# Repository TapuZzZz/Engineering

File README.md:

# ═══════════════════════════════════════════════════════════════════════════════
#                         🔧 ALGORITHM ENGINEERING GUIDE 🔧
# ═══════════════════════════════════════════════════════════════════════════════

> *A comprehensive reference for data structures, algorithms, and graph theory implementations*

---

## 📚 Data Structures

### Stack (LIFO - Last In, First Out)
```
    Push: 3      ┌─────┐
    Push: 2  →   │  3  │
    Push: 1      │  2  │
    Pop: 1       │  1  │
                 └─────┘
```
**Use Cases:** Function call stack, undo/redo, parentheses matching, DFS

---

### Queue (FIFO - First In, First Out)
```
    Enqueue: A   A → B → C → NULL
    Enqueue: B   
    Enqueue: C   (Head)
    Dequeue: A
```
**Use Cases:** BFS, task scheduling, printer queue, message handling

---

### Linked Lists
```
Linear Linked List (LLL)
    ┌─────┬───┐  ┌─────┬───┐  ┌─────┬───┐
    │ 1   │ •─┼─→│ 2   │ •─┼─→│ 3   │ ∅ │
    └─────┴───┘  └─────┴───┘  └─────┴───┘

Circular Linked List (CLLL)
    ┌─────┬───┐  ┌─────┬───┐  ┌─────┬───┐
    │ 1   │ •─┼─→│ 2   │ •─┼─→│ 3   │ •─┐
    └─────┴───┘  └─────┴───┘  └─────┴───┘
         ↑────────────────────────────────┘

Doubly Linked List (DLLL)
    ┌─────┬───┬───┐  ┌─────┬───┬───┐  ┌─────┬───┬───┐
    │ 1   │ ∅ │ •─┼─→│ 2   │ •─┼─→│ 3   │ •─┼─→│ ∅ │
    │     │ ←─┼─│   │     │ ←─┼─│   │     │ ←─┼─│
    └─────┴───┴───┘  └─────┴───┴───┘  └─────┴───┴───┘
```

---

### Trees

#### Binary Tree
```
           ┌─────┐
           │  1  │
         ┌─┴──┬──┴─┐
        ┌─┴─┐┌─┴─┐ │
        │ 2 ││3  │ │
       ┌┴─┐ ││    │ │
       │4 │ ││    │ │
       └──┘ └┘    └─┘
```
**Time Complexity:** O(log n) average, O(n) worst case

#### AVL Tree (Self-Balancing)
```
        ┌────┴────┐
        │    20   │ ↔ Height: 2
      ┌─┴─┐   ┌───┴─┐
      │10 │   │ 30  │ ↔ Height: 1
     ┌┴─┐ │    │  └──┴──┐
     │5 │ │   │15│    40│
```
**Time Complexity:** O(log n) guaranteed

#### K-ary Tree
```
         ┌──────┴──────┐
         │      1      │ K=3 (ternary)
    ┌────┼────┬──────┐
    │    │    │      │
   ┌2┐  ┌3┐  ┌4┐    ┌5┐
```

#### Heap (Binary Heap)
```
Min Heap              Max Heap
      1                    100
    ┌─┴─┐              ┌──┴──┐
    2   3              80    70
   ┌┴┐ ┌┴┐            ┌┴┐  ┌─┴┐
   4 5 6 7           50 40 30 20

Array: [1,2,3,4,5,6,7]    [100,80,70,50,40,30,20]
```
**Use Cases:** Priority queues, heapsort

---

## 🔄 Graph Theory

### Graph Representations
```
Adjacency Matrix          Adjacency List
  0 1 2 3                 0: [1, 2]
0[0 1 1 0]                1: [0, 3]
1[1 0 1 1]                2: [0, 3]
2[1 1 0 1]                3: [1, 2]
3[0 1 1 0]
```

### Graph Traversal

#### Breadth-First Search (BFS)
```
Start: 0
Level 0:  [0]
Level 1:  [1, 2]
Level 2:  [3, 4, 5]
Level 3:  [6, 7, 8]

Use: Shortest path, level order, connected components
```

#### Depth-First Search (DFS)
```
Start: 0
Path 1: 0 → 1 → 3 → (backtrack)
Path 2: 0 → 2 → 4 → 5 → (backtrack)

Use: Topological sort, cycle detection, connected components
```

### Shortest Path Algorithms

#### Dijkstra's Algorithm
```
Finds shortest path from source to all vertices
Time: O((V + E) log V)
Constraints: Non-negative weights only

     2      3
  A ──→ B ──→ C
  │           ↑
  │─────5─────│
```

#### Bellman-Ford Algorithm
```
Finds shortest path, handles negative weights
Time: O(V × E)
Use: Graphs with negative edge weights

     2      3
  A ──→ B ──→ C
  │          ↑
  │────-1────│
```

#### Floyd-Warshall Algorithm
```
All pairs shortest paths
Time: O(V³)
Space: O(V²)

Creates distance matrix for all vertex pairs
```

### Minimum Spanning Tree

#### Kruskal's Algorithm
```
1. Sort edges by weight
2. Add edge if no cycle formed
3. Continue until all vertices connected

Time: O(E log E)
```

#### Prim's Algorithm
```
1. Start from vertex
2. Add minimum weight edge connecting tree to new vertex
3. Repeat until all vertices in tree

Time: O(V²) or O(E log V)
```

### Topological Sort (DAG)
```
Prerequisites: 0 → 1 → 3
              0 → 2 → 3

Order: 0, 1/2, 2/1, 3

Use: Task scheduling, build systems, course prerequisites
```

---

## 📊 Sorting Algorithms

### Comparison-Based Sorts

| Algorithm | Best | Average | Worst | Space | Stable |
|-----------|------|---------|-------|-------|--------|
| **Bubble Sort** | O(n) | O(n²) | O(n²) | O(1) | ✓ |
| **Selection Sort** | O(n²) | O(n²) | O(n²) | O(1) | ✗ |
| **Insertion Sort** | O(n) | O(n²) | O(n²) | O(1) | ✓ |
| **Shell Sort** | O(n) | O(n log² n) | O(n²) | O(1) | ✗ |
| **Merge Sort** | O(n log n) | O(n log n) | O(n log n) | O(n) | ✓ |
| **Quick Sort** | O(n log n) | O(n log n) | O(n²) | O(log n) | ✗ |
| **Heap Sort** | O(n log n) | O(n log n) | O(n log n) | O(1) | ✗ |

### Non-Comparison Sorts

| Algorithm | Time | Space | Conditions |
|-----------|------|-------|-----------|
| **Counting Sort** | O(n + k) | O(k) | Non-negative integers |
| **Bucket Sort** | O(n + k) avg | O(n + k) | Uniformly distributed |
| **Radix Sort** | O(d × n) | O(n + k) | Fixed number of digits |

### Visualization Example: Merge Sort
```
[38, 27, 43, 3, 9, 82, 10]
        ↓ Divide
[38,27] [43,3] [9,82] [10]
        ↓ Merge
[27,38] [3,43] [9,82] [10]
        ↓ Merge Again
    [3,27,38,43]  [9,10,82]
        ↓ Final Merge
  [3,9,10,27,38,43,82]
```

---

## 🔍 Search Algorithms

### Binary Search
```
Sorted Array: [1, 3, 5, 7, 9, 11, 13, 15]
Search for 7:

  L: 0         M: 3         R: 7
  [1, 3, 5, 7, 9, 11, 13, 15]
           ↑
        Found!

Time Complexity: O(log n)
Space Complexity: O(1) or O(log n) recursive
```

---

## 📈 Complexity Analysis

### Big O Notation Hierarchy
```
O(1) ──────────────── Constant
      ↓
O(log n) ───────────── Logarithmic
      ↓
O(n) ───────────────── Linear
      ↓
O(n log n) ─────────── Linearithmic
      ↓
O(n²) ───────────────── Quadratic
      ↓
O(n³) ───────────────── Cubic
      ↓
O(2ⁿ) ───────────────── Exponential
      ↓
O(n!) ──────────────── Factorial
```

### Graph Complexity

| Operation | Adjacency Matrix | Adjacency List |
|-----------|-----------------|----------------|
| Add Edge | O(1) | O(1) |
| Remove Edge | O(1) | O(V) |
| Add Vertex | O(V²) | O(1) |
| Check Edge | O(1) | O(V) |
| Space | O(V²) | O(V + E) |

---

## 💡 Quick Reference

### When to Use Each Structure

```
🔹 Stack → Recursion, undo/redo, parsing
🔹 Queue → BFS, task scheduling
🔹 Linked List → Insertion/deletion heavy workloads
🔹 Tree → Hierarchical data, searching
🔹 Heap → Priority queue, k-th largest/smallest
🔹 Hash Table → Fast lookup, mapping
🔹 Graph → Networks, recommendations, shortest paths
```

### Algorithm Selection Guide

| Problem | Choose | Why |
|---------|--------|-----|
| **Shortest Path** | Dijkstra | Non-negative weights |
| **Shortest Path (negative)** | Bellman-Ford | Handles negatives |
| **All Pairs Shortest** | Floyd-Warshall | Complete info needed |
| **Minimum Span Tree** | Kruskal | Edge-based approach |
| **Task Order** | Topological Sort | DAG processing |
| **Quick Sorting** | Quick Sort | Average O(n log n) |
| **Stable Sort** | Merge Sort | Preserve order |
| **Small Arrays** | Insertion Sort | Low overhead |
| **Search Sorted** | Binary Search | O(log n) lookup |

---

## ✨ Key Takeaways

1. **Choose your tools wisely** - The right data structure determines efficiency
2. **Know your complexity** - Understand best/average/worst cases
3. **Trade-offs matter** - Time vs space, implementation vs performance
4. **Test edge cases** - Empty inputs, single elements, duplicates
5. **Profile first** - Optimize bottlenecks, not everything
6. **Document well** - Future you (and others) will thank you

---

```
╔═══════════════════════════════════════════════════════════════════════════════╗
║                     Happy Coding! 🚀 Build Beautiful Code                     ║
╚═══════════════════════════════════════════════════════════════════════════════╝
```

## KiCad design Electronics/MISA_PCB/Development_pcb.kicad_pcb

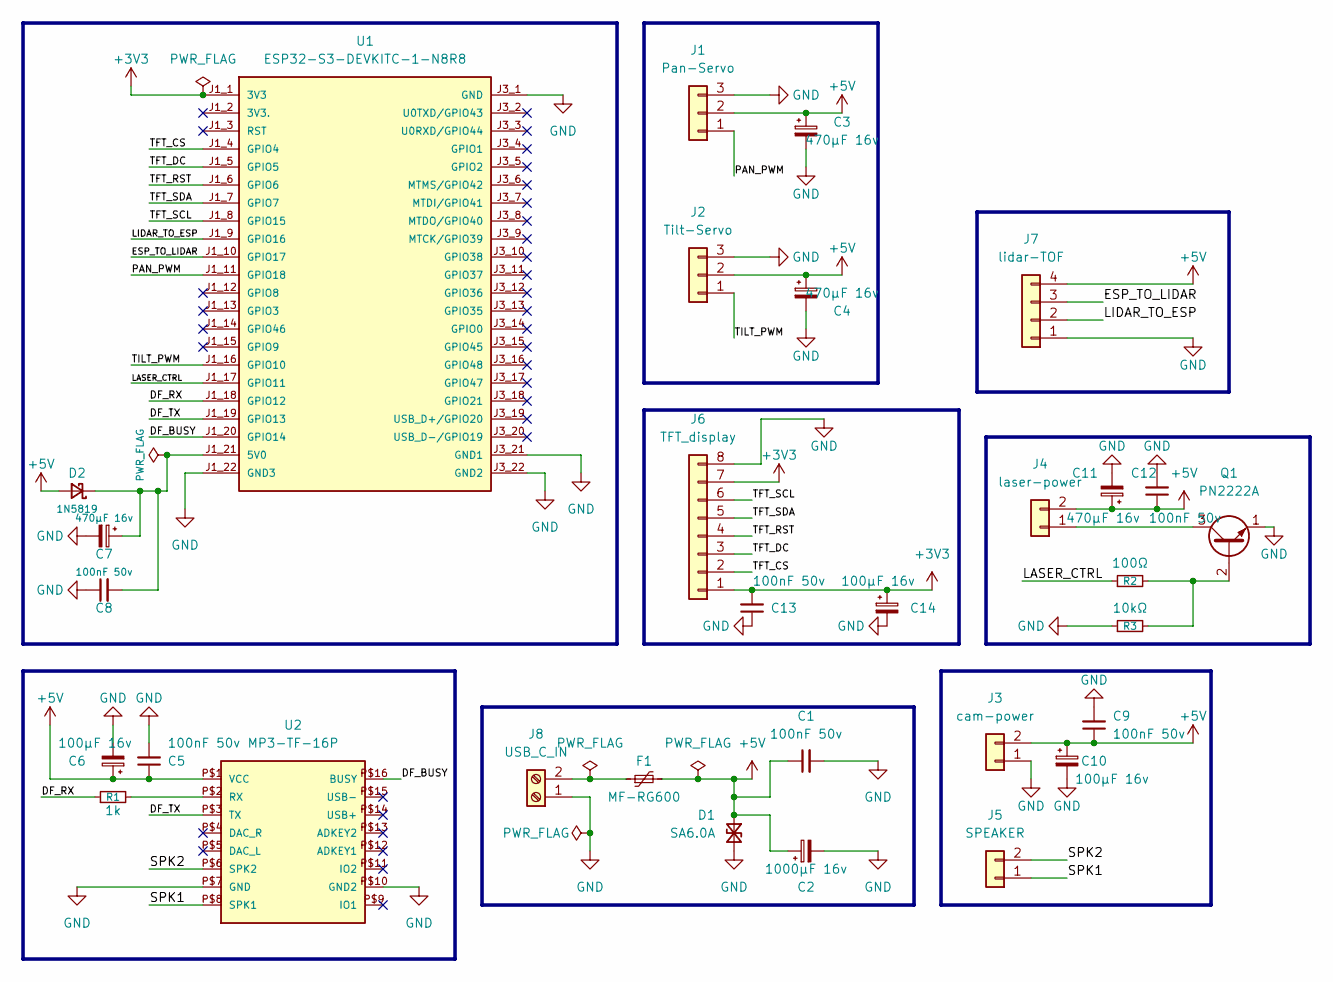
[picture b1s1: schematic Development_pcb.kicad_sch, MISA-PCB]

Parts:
C1, C5, C8, C9, C12, C13: 100nF 50v; C_Disc_D5.0mm_W2.5mm_P2.50mm
C2: 1000µF 16v; CP_Radial_D12.5mm_P5.00mm
C3, C4, C7, C11: 470µF 16v; CP_Radial_D8.0mm_P3.50mm
C6, C10: 100µF 16v; CP_Radial_D6.3mm_P2.50mm
C14: 100µF 16v; CP_Radial_D5.0mm_P2.50mm
D1: SA6.0A; D_DO-15_P10.16mm_Horizontal
D2: 1N5819; D_DO-41_SOD81_P10.16mm_Horizontal
F1: MF-RG600; Fuse_Bourns_MF-RG600
J1: Pan-Servo; JST_XH_B3B-XH-A_1x03_P2.50mm_Vertical
J2: Tilt-Servo; JST_XH_B3B-XH-A_1x03_P2.50mm_Vertical
J3: cam-power; JST_XH_B2B-XH-A_1x02_P2.50mm_Vertical
J4: laser-power; JST_XH_B2B-XH-A_1x02_P2.50mm_Vertical
J5: SPEAKER; JST_XH_B2B-XH-A_1x02_P2.50mm_Vertical
J6: TFT_display; JST_XH_B8B-XH-A_1x08_P2.50mm_Vertical
J7: lidar-TOF; JST_XH_B4B-XH-A_1x04_P2.50mm_Vertical
J8: USB_C_IN; TerminalBlock_Xinya_XY308-2.54-2P_1x02_P2.54mm_Horizontal
Q1: PN2222A; TO-92_Inline
R1: 1k; R_Axial_DIN0207_L6.3mm_D2.5mm_P10.16mm_Horizontal
R2: 100Ω; R_Axial_DIN0207_L6.3mm_D2.5mm_P2.54mm_Vertical
R3: 10kΩ; R_Axial_DIN0207_L6.3mm_D2.5mm_P2.54mm_Vertical
U1: ESP32-S3-DEVKITC-1-N8R8; ESP32-S3-DevKitC-1_Socket
U2: MP3-TF-16P

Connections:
+3V3: C13.2, C14.1, J6.1, J6.7, U1.J1_1 (3V3)
+5V: C1.1, C2.1, C3.1, C4.1, C5.1, C6.1, C9.1, C10.1, C11.1, C12.1, D1.1 (A1), D2.2 (A), F1.2, J1.2, J2.2, J3.2, J4.2, J7.4, U2.P$1 (VCC)
/DF_BUSY: U1.J1_20 (GPIO14), U2.P$16 (BUSY)
/DF_RX: R1.1, U1.J1_18 (GPIO12)
/DF_TX: U1.J1_19 (GPIO13), U2.P$3 (TX)
/ESP_TO_LIDAR: J7.3, U1.J1_10 (GPIO17)
/LASER_CTRL: R2.1, U1.J1_17 (GPIO11)
/LIDAR_TO_ESP: J7.2, U1.J1_9 (GPIO16)
/PAN_PWM: J1.1, U1.J1_11 (GPIO18)
/SPK1: J5.1, U2.P$8 (SPK1)
/SPK2: J5.2, U2.P$6 (SPK2)
/TFT_CS: J6.2, U1.J1_4 (GPIO4)
/TFT_DC: J6.3, U1.J1_5 (GPIO5)
/TFT_RST: J6.4, U1.J1_6 (GPIO6)
/TFT_SCL: J6.6, U1.J1_8 (GPIO15)
/TFT_SDA: J6.5, U1.J1_7 (GPIO7)
/TILT_PWM: J2.1, U1.J1_16 (GPIO10)
GND: C1.2, C2.2, C3.2, C4.2, C5.2, C6.2, C7.2, C8.1, C9.2, C10.2, C11.2, C12.2, C13.1, C14.2, D1.2 (A2), J1.3, J2.3, J3.1, J6.8, J7.1, J8.1, Q1.1 (E), R3.1, U1.J1_22 (GND3), U1.J3_1 (GND), U1.J3_21 (GND1), U1.J3_22 (GND2), U2.P$7 (GND), U2.P$10 (GND2)
unnamed: C7.1, C8.2, D2.1 (K), U1.J1_21 (5V0)
unnamed: J4.1, Q1.3 (C)
unnamed: F1.1, J8.2
unnamed: Q1.2 (B), R2.2, R3.2
unnamed: R1.2, U2.P$2 (RX)

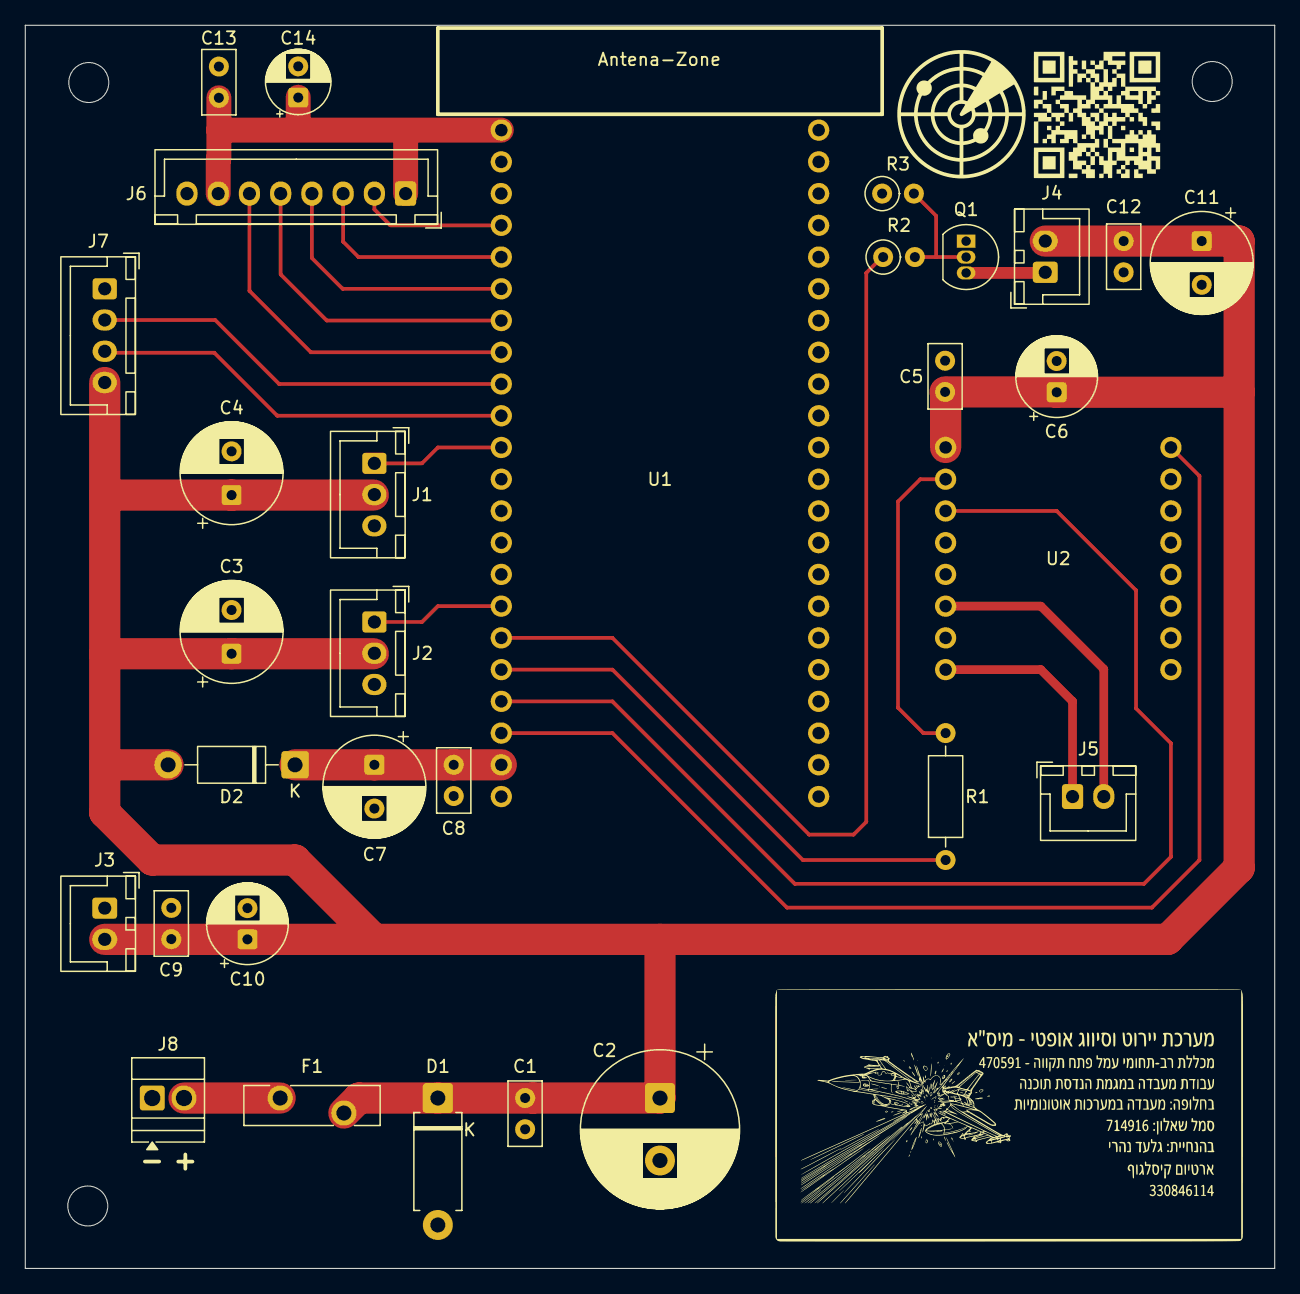
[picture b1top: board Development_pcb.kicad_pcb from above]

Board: 2 copper layers, 100.0 x 99.5 mm, 31 parts (0 on the bottom side), 23 nets.

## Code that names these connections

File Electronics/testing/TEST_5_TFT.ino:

// =================================================================
//  TEST 5 - TFT SCREEN (ST7735) ONLY
//
//  WIRING: CS = GPIO11, RST = GPIO12, DC = GPIO9, MOSI = GPIO10, SCK = GPIO15
// =================================================================

#include <SPI.h>
#include <Adafruit_GFX.h>
#include <Adafruit_ST7735.h>

#define TFT_CS   11
#define TFT_RST  12
#define TFT_DC   9
#define TFT_MOSI 10
#define TFT_SCK  15

class TftWithOffset : public Adafruit_ST7735 {
public:
  TftWithOffset(SPIClass* spiBus, int8_t csPin, int8_t dcPin, int8_t rstPin)
    : Adafruit_ST7735(spiBus, csPin, dcPin, rstPin) {}

  using Adafruit_ST7735::setColRowStart;
};

TftWithOffset tft = TftWithOffset(&SPI, TFT_CS, TFT_DC, TFT_RST);

const int8_t TFT_COL_OFFSET = 2;
const int8_t TFT_ROW_OFFSET = 1;

void setup() {
  Serial.begin(115200);
  delay(1000);

  Serial.println("=== TEST 5: TFT SCREEN ONLY ===");
  Serial.println("CS=11 RST=12 DC=9 MOSI=10 SCK=15");
  Serial.println("");

  pinMode(TFT_RST, OUTPUT);
  digitalWrite(TFT_RST, HIGH);
  delay(100);
  digitalWrite(TFT_RST, LOW);
  delay(100);
  digitalWrite(TFT_RST, HIGH);
  delay(100);

  SPI.begin(TFT_SCK, -1, TFT_MOSI, TFT_CS);
  SPI.setFrequency(1000000);

  tft.initR(INITR_BLACKTAB);
  tft.setRotation(1);
  tft.setColRowStart(TFT_COL_OFFSET, TFT_ROW_OFFSET);

  Serial.println("Screen initialized. Running color fill test...");

  tft.fillScreen(ST7735_RED);
  Serial.println("RED - check full panel is red, no dead areas.");
  delay(1000);

  tft.fillScreen(ST7735_GREEN);
  Serial.println("GREEN");
  delay(1000);

  tft.fillScreen(ST7735_BLUE);
  Serial.println("BLUE");
  delay(1000);

  tft.fillScreen(ST7735_WHITE);
  Serial.println("WHITE - look closely for any noisy/misaligned edge.");
  delay(1000);

  tft.fillScreen(ST7735_BLACK);

  tft.drawRect(0, 0, tft.width(), tft.height(), ST7735_YELLOW);

  tft.setTextColor(ST7735_WHITE);
  tft.setTextSize(1);
  tft.setCursor(10, 10);
  tft.print("TFT TEST OK");
  tft.setCursor(10, 25);
  tft.print("Border should be flush");
  tft.setCursor(10, 40);
  tft.print("on all 4 edges.");

  Serial.println("Border + text drawn. Check border alignment on all edges.");
  Serial.println("");
  Serial.println("=== TEST COMPLETE ===");
}

void loop() {

}

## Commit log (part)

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2025-08-04 Engineering studies - initial commit
2025-08-04 Add .gitkeep files to preserve empty directories
2025-08-04 Fix Q folder numbering for proper sorting
2025-08-04 Fix all folder numbering for proper sorting (Q01, Q02, etc.)
2025-08-04 fix error
2025-08-04 test
2025-08-04 creation of new q
2025-08-12 12-14
2025-12-16 change
2025-12-16 Main
2025-12-16 New File
2025-12-16 I add 1
2025-12-16 i add
2025-12-16 Add multiple lines of '3' to Three.txt
    Inserted multiple lines of '3' into Three.txt.
2025-12-16 Change Three AND Create agam
2025-12-16 Append Rosh Haayin to agam.txt
2025-12-24 Add C learning files
2025-12-24 files
2025-12-24 add return
2025-12-24 Changes in Node
2025-12-25 check home branch
2025-12-25 Change in lll
2025-12-25 tree
2025-12-25 heap
2025-12-25 tree deleted
2025-12-26 Add doubly linked list implementation and remove tree structure
2025-12-26 Implement InsertNext_DLLL function and add stubs for Pop_DLLL and Delete_DLLL
2025-12-26 Implement doubly linked list (DLL) and circular doubly linked list (CDLL) functionalities
2025-12-26 stack ready
2025-12-31 Add line
2025-12-31 change in dclll and file in c
2026-01-01 remove unused student management code
2026-01-01 changes in names
2026-01-01 Refactor data structure definitions to remove redundant 'struct' keyword usage
2026-01-01 Fix struct member declarations in BinNode for clarity and consistency
2026-01-01 Remove unused tree initialization in main function
2026-01-01 Remove commented-out stack operations from main function
2026-01-01 Fix struct member declarations and refactor queue functions for consistency
2026-01-02 Fix formatting in main function for consistency
2026-01-02 cheating .h files
2026-01-02 alot of changes
2026-01-02 mission done
2026-01-03 spacing
2026-01-03 changes in trees
2026-01-04 task nili trees
2026-01-04 refactor: update function signatures from ThreeNode to BinNode for consistency
2026-01-05 q7 nili
2026-01-05 nili mission finished
2026-01-06 chore: remove unnecessary .DS_Store files
2026-01-09 feat: implement Heap data structure with basic operations
2026-01-09 feat: add initial implementation of Priority Queue data structure
2026-01-14 chore: remove unused Priority Queue implementation files
2026-01-14 feat: add Binary Tree, Trinary Tree, and K-Tree implementations with header files
2026-01-17 feat: add initial implementation of AVL Tree with header file
2026-01-18 feat: add initial implementation of Graph data structure with header file
2026-01-19 feat: add initial implementation of TheWikiGame script
2026-01-22 sorthing
2026-01-22 name correction
2026-01-23 feat: implement graph operations including matrix multiplication and path finding
2026-01-25 refactor: remove unused graph operations and executable
2026-01-29 refactor: Update StackNode struct definition to explicitly use `struct StackNode *next` and adjust code formatting.
2026-02-01 rename
2026-02-01 feat: add initial HashTable implementation files
2026-02-03 feat: add HashTable implementation files
2026-02-03 feat: add graph algorithms implementations for BFS, DFS, Dijkstra, Bellman-Ford, and spanning trees
2026-02-03 refactor: remove Binary Search implementation
2026-02-03 feat: add 5_DagTopologicallyOrdered.c for DAG topological ordering
2026-02-19 I did Exchange Sort !!!!!!
2026-02-19 i did Selection sort!!!!!!
2026-02-19 little fixes
2026-02-19 Space Complexity: O(1)
2026-02-20 insertionsort
2026-02-21 feat: Add VS Code C/C++ debugging and IntelliSense configurations and refactor Bucket Sort to handle integers with dynamic range and dynamic bucket resizing.
2026-02-21 feat: Implement Radix Sort, Merge Sort, and Counting Sort algorithms.
2026-02-21 feat: Implement Heap Sort, Binary Search, and Quick Sort algorithms in C, and remove a compiled object file.
2026-02-21 feat: delete BinarySearch and QuickSort implementations, and modify ExchangeSort, SelectionSort, and InsertionSort.
2026-02-21 Just Chang
2026-02-22 chore: delete an unspecified file.
2026-02-23 feat: Implement Floyd-Warshall algorithm for shortest path calculation
2026-02-23 feat: Implement Kruskal's and Prim's algorithms for minimum spanning tree
2026-02-24 feat: Add Wikipedia Bidirectional BFS implementation with ncurses visualization
2026-02-25 fix: Remove duplicate comment for Log ring buffer structure
2026-02-25 chore: Remove unused Wikipedia Bidirectional BFS implementation
2026-02-26 refactor: Change stack and queue data types from int to void* for generic usage
2026-02-26 style: Adjust pointer formatting for consistency in stack and queue implementations
2026-02-26 main change in lll
2026-02-28 changes in clll
2026-02-28 data structures
2026-02-28 final fix in the stack and the queue
2026-03-01 changes in lll
2026-03-01 update README.md to enhance algorithm engineering guide with detailed data structures and algorithms
2026-03-02 add graph algorithms: implement Floyd-Warshall, Kruskal's, and Prim's algorithms
2026-03-02 START OF PROJECT
2026-03-14 remove unused data structures and initialization functions from main.c
2026-03-20 Refactor sorting algorithms and add binary search implementation
    - Removed implementations of Exchange Sort, Selection Sort, Insertion Sort, Bucket Sort, Shell Sort, Counting Sort, Radix Sort, Merge Sort, and Quick Sort from the SortingAlgorithms directory.
    - Added new implementations of Exchange Sort, Selection Sort, Insertion Sort, Bucket Sort, Shell Sort, Counting Sort, Radix Sort, Merge Sort, and Quick Sort to the Algorithms directory.
    - Introduced a new binary search implementation with both iterative and recursive methods.
    - Updated documentation for each sorting algorithm to include time complexity, space complexity, and stability.
2026-03-23 add client-server communication implementation with socket programming
2026-04-07 remove unused client, server, crawler, query implementations and database file
2026-04-07 Add initial implementation of strings.c with main function and email verification stub
2026-04-07 Remove strings.c and add initial implementation of Bank.c with file handling and menu options
2026-04-08 Add initial implementation of test.c with various mathematical functions and user input handling
2026-04-09 Remove unused Bank.c and test.c files to clean up the repository
2026-04-12 Add initial implementation of app.asm for recursive factorial calculation
2026-04-13 Refactor app.asm to remove factorial calculation and implement even number counting
2026-04-14 Add countEven.asm for counting even numbers in an array
2026-04-14 Add initial implementation of BubbleSort.asm for sorting an array
2026-04-26 Add IronWing SQL Project PDF to the repository
2026-05-14 Add initial configuration files for SQL project in .idea directory
2026-05-14 removed some files
2026-05-18 scapy
2026-05-19 19.5
2026-05-20 Add initial resume HTML structure with styling and content
2026-05-20 Remove obsolete resume HTML and image files; add initial Jupyter notebook for Python example
2026-05-21 Add basic HTTP server with user authentication and chat functionality
    - Implemented a simple HTTP server in Python that handles user login and chat messages.
    - Created a login page (login.html) for user authentication.
    - Added secure home page (secure_home.html) displaying chat messages and user information.
    - Introduced session management to keep track of logged-in users.
    - Allowed admin users to access a restricted admin panel with system stats.
    - Implemented message sending and displaying functionality in the chat room.
2026-05-26 creating nslookup 25.5.26
2026-05-26 changes in the nslookup
2026-05-30 networks folder
2026-06-04 Dns spoofing
2026-06-04 chnaged name
2026-06-06 Remove unnecessary whitespace in MyNSlookup.py
2026-06-06 client server
2026-06-06 Add client and server implementation files to Networks directory
2026-06-07 avl tree done at the middle of the night
2026-06-19 lagami arp
2026-06-23 feat: initialize Angular application with basic structure and styles
    - Added app component with HTML and CSS files.
    - Created routing configuration file.
    - Implemented basic unit tests for the app component.
    - Set up main entry point and index HTML file.
    - Configured TypeScript settings for the application and tests.
    - Included global styles and placeholder content in the app.
2026-06-23 feat: add VSCode settings for Angular strict mode prompt
2026-06-23 refactor: remove app component and related files
    - Deleted app.html, app.routes.ts, app.spec.ts, app.ts, index.html, main.ts, styles.css, tsconfig.app.json, tsconfig.json, and tsconfig.spec.json.
    - This cleanup removes the app component and its associated files, streamlining the project structure.
2026-06-24 Learning Angular
2026-06-24 feat: update app layout and introduce username display
    - Removed placeholder content from app.html and added a personalized greeting with the username.
    - Introduced a new property `username` in app.ts to hold the user's name.
    - Cleaned up unnecessary styles and elements in app.html for a more streamlined appearance.
    - Added a new .DS_Store file and an empty Icon file to the project structure.
2026-06-26 feat: implement user input fields and age validation in app component
2026-06-28 feat: initialize PitchPulse application with Angular setup
    - Add package.json with Angular dependencies and scripts
    - Create favicon.ico for the application
    - Set up app configuration in app.config.ts
    - Add global styles in app.css
    - Implement main application structure in app.ts, app.html, and app.css
    - Define application routes in app.routes.ts
2026-06-28 feat: Implement Navbar and Routing Structure
    - Added a Navbar component with responsive design and mobile menu functionality.
    - Created Home, About, and Features pages with basic content and styles.
    - Established routing for the application, including a default route and a wildcard redirect.
    - Introduced global styles for the application and specific styles for the Navbar and pages.
    - Implemented wave animation in the Home component to enhance user experience.
